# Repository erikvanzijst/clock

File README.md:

# 24H Digital Clock

This project contains the schematics and PCB layout for a 24-hour digital
quartz clock with self-dimming LED display.

Full write-up is at https://medium.com/@erikvanzijst/a-digital-quartz-clock-from-scratch-a80ec5e427

## Kicad symbol and footprint libraries
The project uses the [DigiKey Kicad symbol and footprint libraries](https://github.com/Digi-Key/digikey-kicad-library).
After cloning or downloading those locally, [add them to the Kicad Symbol and
Footprint libraries](https://forum.digikey.com/t/importing-the-digi-key-kicad-library-into-kicad-5-0-0/4075).

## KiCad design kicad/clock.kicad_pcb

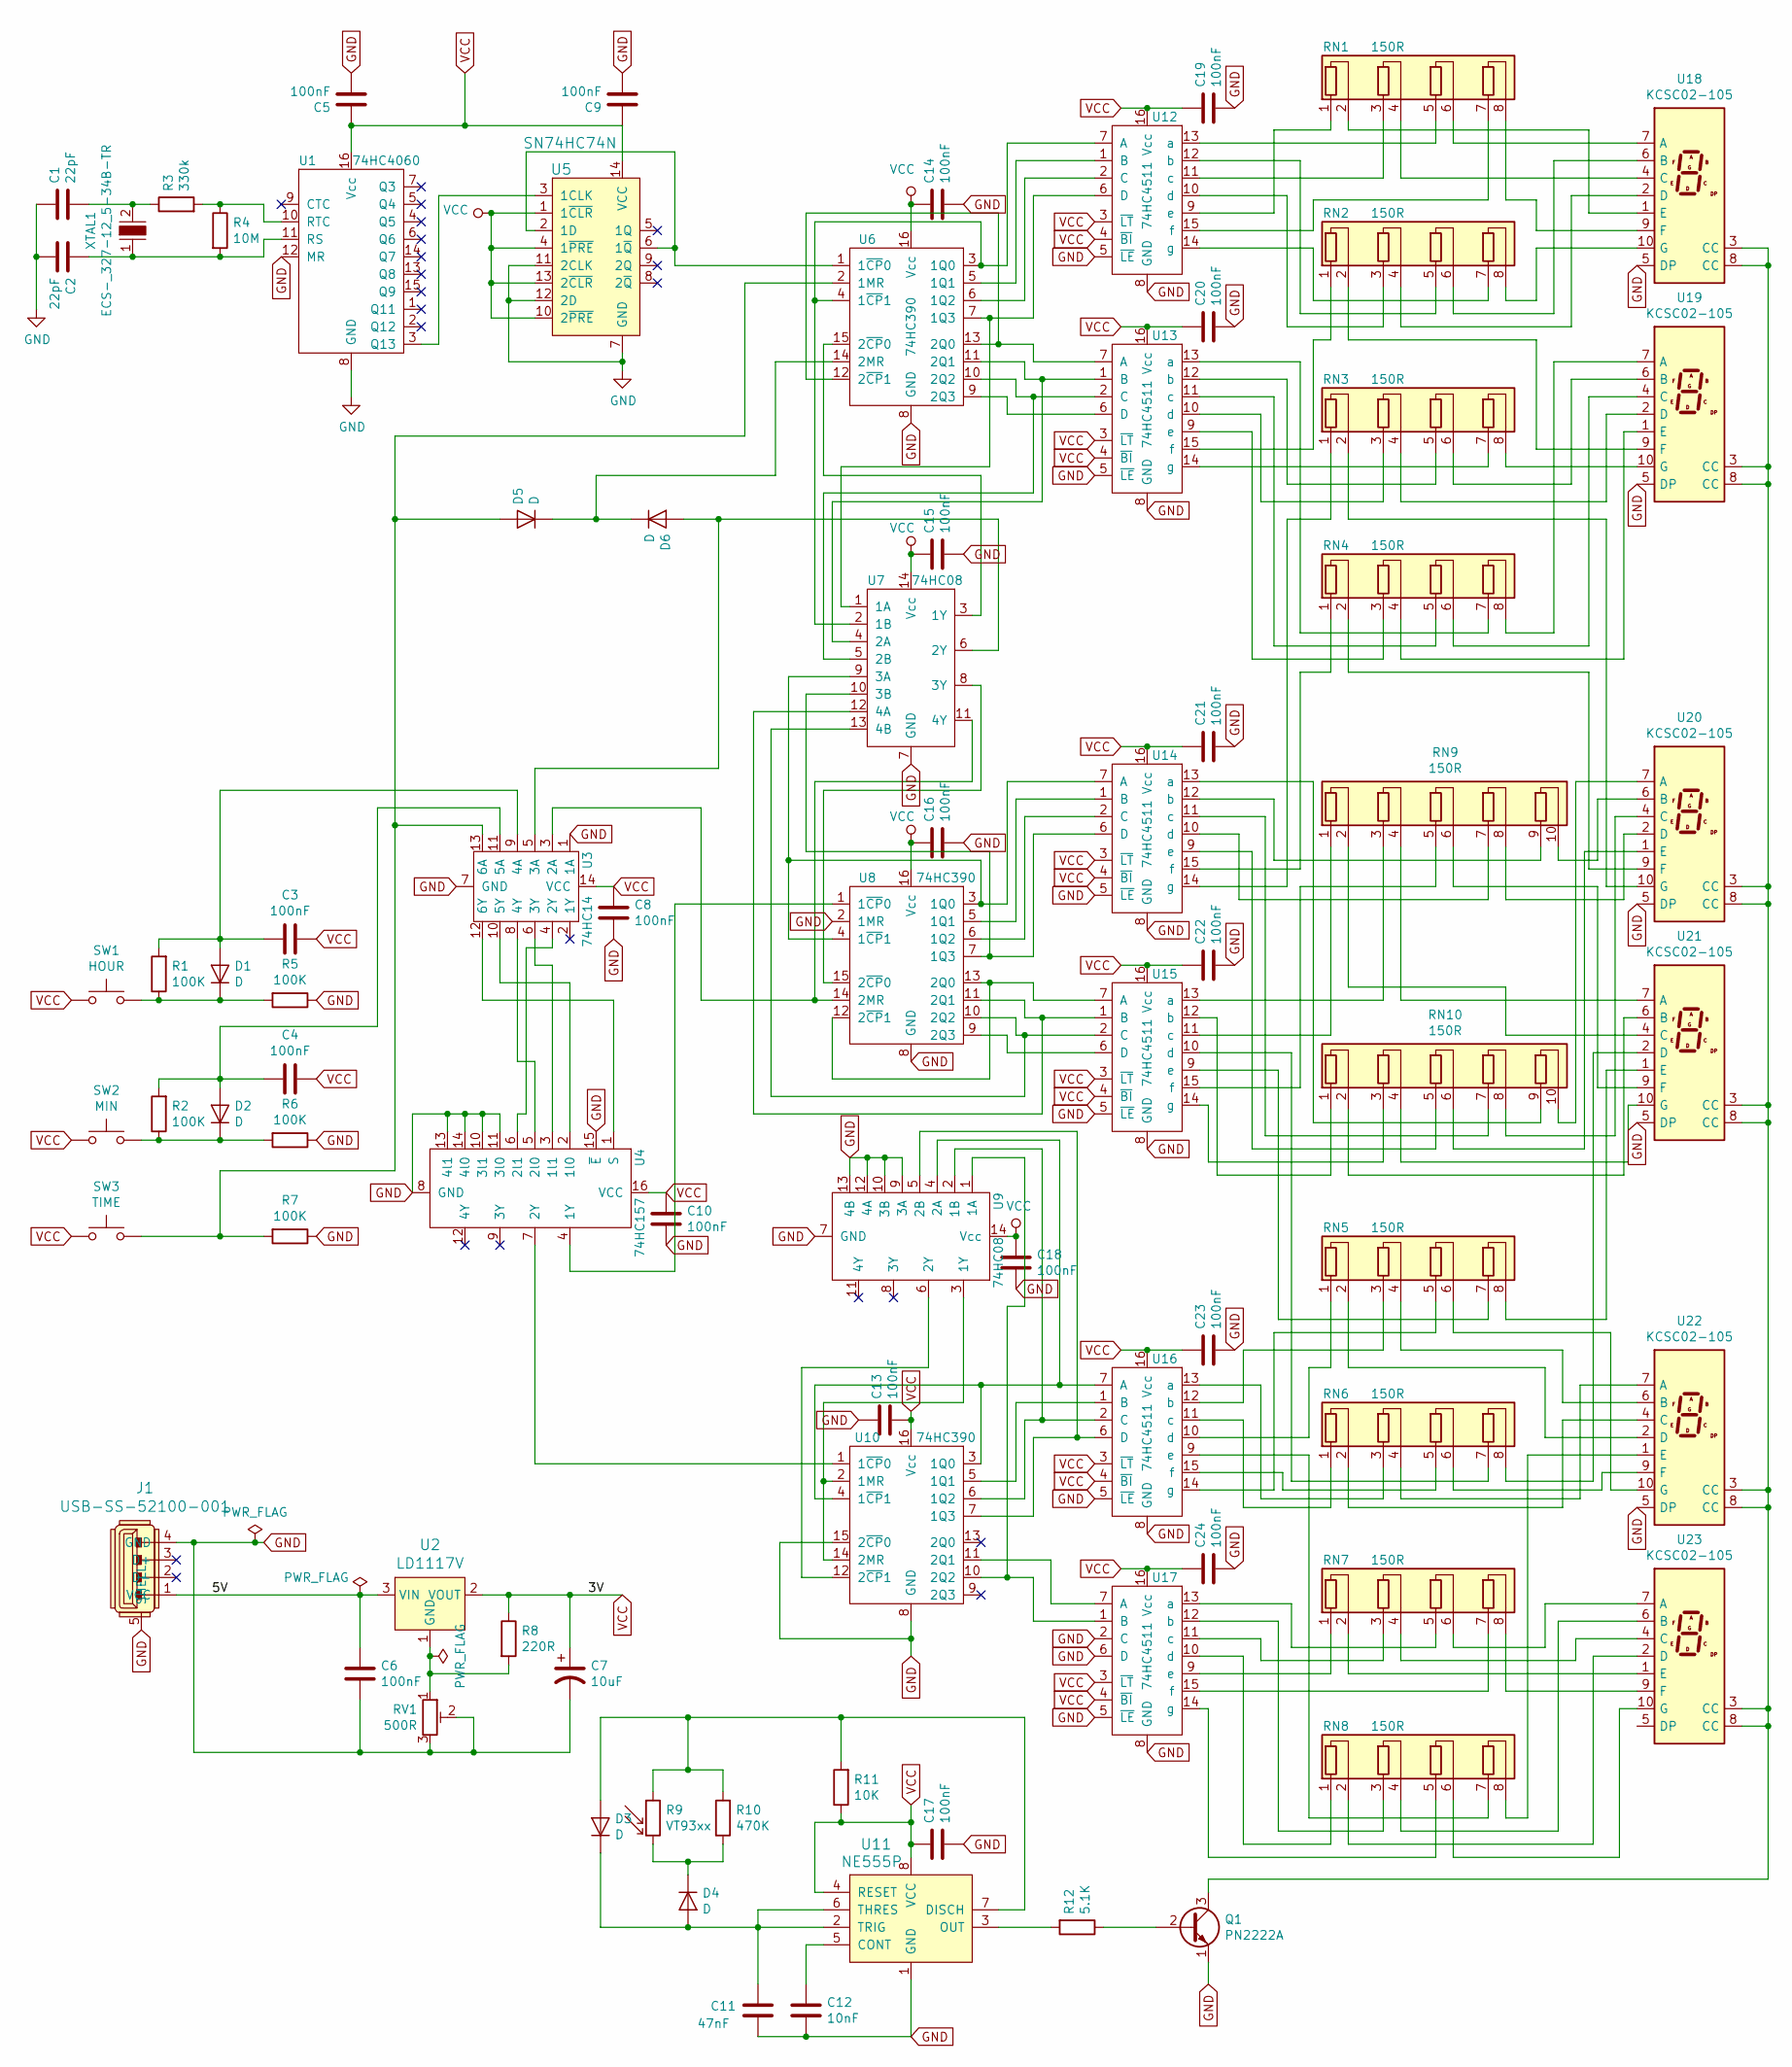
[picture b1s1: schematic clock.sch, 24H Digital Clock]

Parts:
C1, C2: 22pF; C_Disc_D5.0mm_W2.5mm_P2.50mm
C3, C4, C5, C6, C8, C9, C10, C13, C14, C15, C16, C17, C18, C19, C20, C21, C22, C23, C24: 100nF; C_Disc_D5.0mm_W2.5mm_P2.50mm
C7: 10uF; CP_Radial_Tantal_D5.0mm_P2.50mm
C11: 47nF; C_Disc_D5.0mm_W2.5mm_P2.50mm
C12: 10nF; C_Disc_D5.0mm_W2.5mm_P2.50mm
D1, D2, D3, D4, D5, D6: D; Diode_DO-35_P10mm
J1: USB-SS-52100-001; USB_A_Stewart_SS-52100-001_Horizontal; MPN SS-52100-001; Digi-Key_PN 380-1412-ND
Q1: PN2222A; TO-92_Inline_Wide
R1, R2, R5, R6, R7: 100K; R_Axial_DIN0207_L6.3mm_D2.5mm_P7.62mm_Horizontal
R3: 330k; R_Axial_DIN0207_L6.3mm_D2.5mm_P7.62mm_Horizontal
R4: 10M; R_Axial_DIN0207_L6.3mm_D2.5mm_P7.62mm_Horizontal
R8: 220R; R_Axial_DIN0207_L6.3mm_D2.5mm_P7.62mm_Horizontal
R9: VT93xx; R_LDR_4.9x4.2mm_P2.54mm_Vertical
R10: 470K; R_Axial_DIN0207_L6.3mm_D2.5mm_P7.62mm_Horizontal
R11: 10K; R_Axial_DIN0207_L6.3mm_D2.5mm_P7.62mm_Horizontal
R12: 5.1K; R_Axial_DIN0207_L6.3mm_D2.5mm_P7.62mm_Horizontal
RN1, RN2, RN3, RN4, RN5, RN6, RN7, RN8: 150R; R_Array_SIP8
RN9, RN10: 150R; R_Array_SIP10
RV1: 500R; Potentiometer_Bourns_3339P_Vertical_HandSoldering
SW1: HOUR; SW_PUSH_6mm_H4.3mm
SW2: MIN; SW_PUSH_6mm_H4.3mm
SW3: TIME; SW_PUSH_6mm_H4.3mm
U1: 74HC4060; DIP-16_W7.62mm_Socket
U2: LD1117V; TO-220-3; MPN LD1117V; Digi-Key_PN 497-7310-5-ND
U3: 74HC14; Socket_DIP-14_0.775in_Conn
U4: 74HC157; DIP-16_W7.62mm_Socket
U5: SN74HC74N; Socket_DIP-14_0.775in_Conn; MPN SN74HC74N; Digi-Key_PN 296-1602-5-ND
U6, U8, U10: 74HC390; DIP-16_W7.62mm_Socket
U7, U9: 74HC08; Socket_DIP-14_0.775in_Conn
U11: NE555P; DIP-8_W7.62mm_Socket; MPN NE555P; Digi-Key_PN 296-1411-5-ND
U12, U13, U14, U15, U16, U17: 74HC4511; DIP-16_W7.62mm_Socket
U18, U19, U20, U21, U22, U23: KCSC02-105; 7SegmentLED_LTS6760_LTS6780
XTAL1: ECS-_327-12_5-34B-TR; Crystal_DS26_D2.0mm_L6.0mm_Horizontal; MPN ECS-.327-12.5-34B-TR; Digi-Key_PN XC1617CT-ND

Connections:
/5V: C6.1, J1.1 (VCC), U2.3 (VIN)
GND: C1.1, C2.2, C5.2, C6.2, C7.2, C8.2, C9.2, C10.2, C11.2, C12.2, C13.1, C14.2, C15.2, C16.2, C17.2, C18.2, C19.2, C20.2, C21.2, C22.2, C23.2, C24.2, J1.4 (GND), J1.5 (SHELL), Q1.1 (E), R5.1, R6.1, R7.1, RV1.2, RV1.3, U1.8 (GND), U1.12 (MR), U3.1 (1A), U3.7 (GND), U4.8 (GND), U4.10 (3l1), U4.11 (3l0), U4.13 (4l1), U4.14 (4l0), U4.15 (~E), U5.7 (GND), U5.11 (2CLK), U5.12 (2D), U6.8 (GND), U7.7 (GND), U8.2 (1MR), U8.8 (GND), U9.7 (GND), U9.9 (3A), U9.10 (3B), U9.12 (4A), U9.13 (4B), U10.8 (GND), U10.15 (2~CP~0), U11.1 (GND), U12.5 (~LE), U12.8 (GND), U13.5 (~LE), U13.8 (GND), U14.5 (~LE), U14.8 (GND), U15.5 (~LE), U15.8 (GND), U16.5 (~LE), U16.8 (GND), U17.2 (C), U17.5 (~LE), U17.6 (D), U17.8 (GND), U18.5 (DP), U19.5 (DP), U20.5 (DP), U21.5 (DP), U22.5 (DP)
unnamed: C1.2, R3.1, XTAL1.2
unnamed: C2.1, R4.2, U1.11 (RS), XTAL1.1
unnamed: C3.2, D1.2 (A), R1.2, U3.9 (4A)
unnamed: C4.2, D2.2 (A), R2.2, U3.11 (5A)
unnamed: C11.1, D3.1 (K), D4.2 (A), U11.2 (TRIG), U11.6 (THRES)
unnamed: C12.1, U11.5 (CONT)
unnamed: D1.1 (K), R1.1, R5.2, SW1.2
unnamed: D2.1 (K), R2.1, R6.2, SW2.2
unnamed: D3.2 (A), R9.1, R10.2, R11.2, U11.7 (DISCH)
unnamed: D4.1 (K), R9.2, R10.1
unnamed: D5.1 (K), D6.1 (K), U6.14 (2MR)
unnamed: D5.2 (A), R7.2, SW3.2, U3.13 (6A), U6.2 (1MR)
unnamed: D6.2 (A), U3.5 (3A), U7.6 (2Y)
unnamed: Q1.2 (B), R12.1
unnamed: Q1.3 (C), U18.3 (CC), U18.8 (CC), U19.3 (CC), U19.8 (CC), U20.3 (CC), U20.8 (CC), U21.3 (CC), U21.8 (CC), U22.3 (CC), U22.8 (CC), U23.3 (CC), U23.8 (CC)
unnamed: R3.2, R4.1, U1.10 (RTC)
unnamed: R8.2, RV1.1, U2.1 (GND)
unnamed: R12.2, U11.3 (OUT)
unnamed: RN1.1 (R1.1), U12.9 (e)
unnamed: RN1.2 (R1.2), U18.1 (E)
unnamed: RN1.3 (R2.1), U12.11 (c)
unnamed: RN1.4 (R2.2), U18.4 (C)
unnamed: RN1.5 (R3.1), U12.13 (a)
unnamed: RN1.6 (R3.2), U18.7 (A)
unnamed: RN1.7 (R4.1), U12.15 (f)
unnamed: RN1.8 (R4.2), U18.9 (F)
unnamed: RN2.1 (R1.1), U13.15 (f)
unnamed: RN2.2 (R1.2), U19.9 (F)
unnamed: RN2.3 (R2.1), U12.10 (d)
unnamed: RN2.4 (R2.2), U18.2 (D)
unnamed: RN2.5 (R3.1), U12.12 (b)
unnamed: RN2.6 (R3.2), U18.6 (B)
unnamed: RN2.7 (R4.1), U12.14 (g)
unnamed: RN2.8 (R4.2), U18.10 (G)
unnamed: RN3.1 (R1.1), U14.14 (g)
unnamed: RN3.2 (R1.2), U20.10 (G)
unnamed: RN3.3 (R2.1), U13.10 (d)
unnamed: RN3.4 (R2.2), U19.2 (D)
unnamed: RN3.5 (R3.1), U13.12 (b)
unnamed: RN3.6 (R3.2), U19.6 (B)
unnamed: RN3.7 (R4.1), U13.14 (g)
unnamed: RN3.8 (R4.2), U19.10 (G)
unnamed: RN4.1 (R1.1), U14.15 (f)
unnamed: RN4.2 (R1.2), U20.9 (F)
unnamed: RN4.3 (R2.1), U13.9 (e)
unnamed: RN4.4 (R2.2), U19.1 (E)
unnamed: RN4.5 (R3.1), U13.11 (c)
unnamed: RN4.6 (R3.2), U19.4 (C)
unnamed: RN4.7 (R4.1), U13.13 (a)
unnamed: RN4.8 (R4.2), U19.7 (A)
unnamed: RN5.1 (R1.1), U16.10 (d)
unnamed: RN5.2 (R1.2), U22.2 (D)
unnamed: RN5.3 (R2.1), U16.12 (b)
unnamed: RN5.4 (R2.2), U22.6 (B)
unnamed: RN5.5 (R3.1), U16.14 (g)
unnamed: RN5.6 (R3.2), U22.10 (G)
unnamed: RN5.7 (R4.1), U15.9 (e)
unnamed: RN5.8 (R4.2), U21.1 (E)
unnamed: RN6.1 (R1.1), U16.11 (c)
unnamed: RN6.2 (R1.2), U22.4 (C)
unnamed: RN6.3 (R2.1), U16.13 (a)
unnamed: RN6.4 (R2.2), U22.7 (A)
unnamed: RN6.5 (R3.1), U16.15 (f)
unnamed: RN6.6 (R3.2), U22.9 (F)
unnamed: RN6.7 (R4.1), U15.10 (d)
unnamed: RN6.8 (R4.2), U21.2 (D)
unnamed: RN7.1 (R1.1), U17.9 (e)
unnamed: RN7.2 (R1.2), U23.1 (E)
unnamed: RN7.3 (R2.1), U17.11 (c)
unnamed: RN7.4 (R2.2), U23.4 (C)
unnamed: RN7.5 (R3.1), U17.13 (a)
unnamed: RN7.6 (R3.2), U23.7 (A)
unnamed: RN7.7 (R4.1), U17.15 (f)
unnamed: RN7.8 (R4.2), U23.9 (F)
unnamed: RN8.1 (R1.1), U17.10 (d)
unnamed: RN8.2 (R1.2), U23.2 (D)
unnamed: RN8.3 (R2.1), U17.12 (b)
unnamed: RN8.4 (R2.2), U23.6 (B)
unnamed: RN8.5 (R3.1), U17.14 (g)
unnamed: RN8.6 (R3.2), U23.10 (G)
unnamed: RN8.7 (R4.1), U16.9 (e)
unnamed: RN8.8 (R4.2), U22.1 (E)
unnamed: RN9.1 (R1.1), U15.11 (c)
unnamed: RN9.2 (R1.2), U21.4 (C)
unnamed: RN9.3 (R2.1), U15.13 (a)
unnamed: RN9.4 (R2.2), U21.7 (A)
unnamed: RN9.5 (R3.1), U15.15 (f)
unnamed: RN9.6 (R3.2), U21.9 (F)
unnamed: RN9.7 (R4.1), U14.10 (d)
unnamed: RN9.8 (R4.2), U20.2 (D)
unnamed: RN9.9 (R5.1), U14.12 (b)
unnamed: RN9.10 (R5.2), U20.6 (B)
unnamed: RN10.1 (R1.1), U15.12 (b)
unnamed: RN10.2 (R1.2), U21.6 (B)
unnamed: RN10.3 (R2.1), U15.14 (g)
unnamed: RN10.4 (R2.2), U21.10 (G)
unnamed: RN10.5 (R3.1), U14.9 (e)
unnamed: RN10.6 (R3.2), U20.1 (E)
unnamed: RN10.7 (R4.1), U14.11 (c)
unnamed: RN10.8 (R4.2), U20.4 (C)
unnamed: RN10.9 (R5.1), U14.13 (a)
unnamed: RN10.10 (R5.2), U20.7 (A)
unnamed: U1.3 (Q13), U5.3 (1CLK)
unnamed: U3.3 (2A), U7.11 (4Y), U8.14 (2MR)
unnamed: U3.4 (2Y), U4.6 (2l1)
unnamed: U3.6 (3Y), U4.3 (1l1)
unnamed: U3.8 (4Y), U4.5 (2l0)
unnamed: U3.10 (5Y), U4.2 (1l0)
unnamed: U3.12 (6Y), U4.1 (S)
unnamed: U4.4 (1Y), U8.1 (1~CP~0)
unnamed: U5.2 (1D), U5.6 (1~Q), U6.1 (1~CP~0)
unnamed: U6.15 (2~CP~0), U7.3 (1Y)
unnamed: U7.8 (3Y), U8.15 (2~CP~0)
unnamed: U4.7 (2Y), U10.1 (1~CP~0)
unnamed: U9.4 (2A), U10.3 (1Q0), U10.4 (1~CP~1), U16.7 (A)
unnamed: U10.5 (1Q1), U16.1 (B)
unnamed: U9.2 (1B), U10.6 (1Q2), U16.2 (C)
unnamed: U9.5 (2B), U10.7 (1Q3), U16.6 (D)
unnamed: U9.1 (1A), U10.10 (2Q2), U17.1 (B)
unnamed: U10.11 (2Q1), U17.7 (A)
unnamed: U9.6 (2Y), U10.12 (2~CP~1)
unnamed: U9.3 (1Y), U10.2 (1MR), U10.14 (2MR)
unnamed: U6.5 (1Q1), U12.1 (B)
unnamed: U6.6 (1Q2), U12.2 (C)
unnamed: U6.7 (1Q3), U7.1 (1A), U12.6 (D)
unnamed: U6.3 (1Q0), U6.4 (1~CP~1), U7.2 (1B), U12.7 (A)
unnamed: U6.11 (2Q1), U7.4 (2A), U13.1 (B)
unnamed: U6.10 (2Q2), U7.5 (2B), U13.2 (C)
unnamed: U6.9 (2Q3), U13.6 (D)
unnamed: U6.12 (2~CP~1), U6.13 (2Q0), U13.7 (A)
unnamed: U8.5 (1Q1), U14.1 (B)
unnamed: U8.6 (1Q2), U14.2 (C)
unnamed: U7.10 (3B), U8.7 (1Q3), U14.6 (D)
unnamed: U7.9 (3A), U8.3 (1Q0), U8.4 (1~CP~1), U14.7 (A)
unnamed: U7.12 (4A), U8.11 (2Q1), U15.1 (B)
unnamed: U7.13 (4B), U8.10 (2Q2), U15.2 (C)
unnamed: U8.9 (2Q3), U15.6 (D)
unnamed: U8.12 (2~CP~1), U8.13 (2Q0), U15.7 (A)
VCC: C3.1, C4.1, C5.1, C7.1, C8.1, C9.1, C10.1, C13.2, C14.1, C15.1, C16.1, C17.1, C18.1, C19.1, C20.1, C21.1, C22.1, C23.1, C24.1, R8.1, R11.1, SW1.1, SW2.1, SW3.1, U1.16 (Vcc), U2.2 (VOUT), U3.14 (VCC), U4.16 (VCC), U5.1 (1~CLR), U5.4 (1~PRE), U5.10 (2~PRE), U5.13 (2~CLR), U5.14 (VCC), U6.16 (Vcc), U7.14 (Vcc), U8.16 (Vcc), U9.14 (Vcc), U10.16 (Vcc), U11.4 (RESET), U11.8 (VCC), U12.3 (~LT), U12.4 (~BI), U12.16 (Vcc), U13.3 (~LT), U13.4 (~BI), U13.16 (Vcc), U14.3 (~LT), U14.4 (~BI), U14.16 (Vcc), U15.3 (~LT), U15.4 (~BI), U15.16 (Vcc), U16.3 (~LT), U16.4 (~BI), U16.16 (Vcc), U17.3 (~LT), U17.4 (~BI), U17.16 (Vcc)

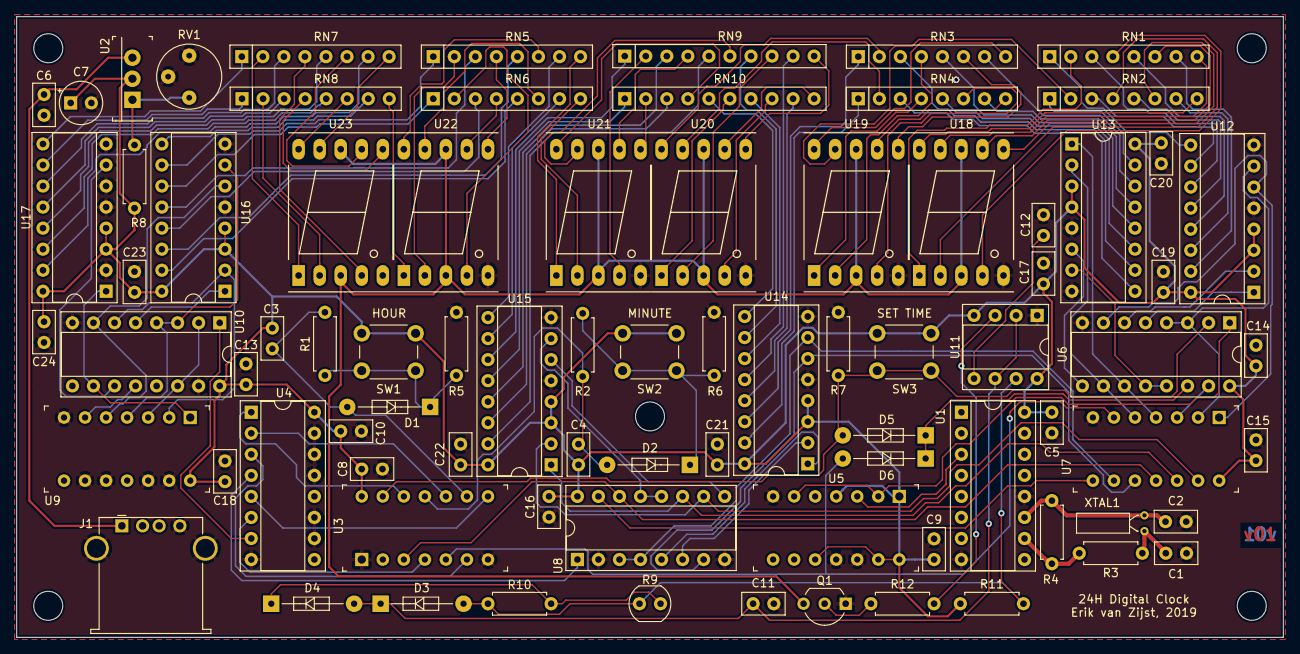
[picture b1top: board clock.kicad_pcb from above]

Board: 2 copper layers, 152.9 x 74.9 mm, 82 parts (0 on the bottom side), 141 nets.

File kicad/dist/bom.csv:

Reference, Quantity, Value,MPN,Digikey Part Number,Price,Total Price,Part Page, Footprint, Category, DK_Datasheet_Link, DK_Detail_Page, Description, Digi-Key_PN, Family, MPN, Manufacturer, Status
C11 ,1,47nF,,,,,,Capacitor_THT:C_Disc_D5.0mm_W2.5mm_P2.50mm,,,,,,,,,
C12 ,1,10nF,,,,,,Capacitor_THT:C_Disc_D5.0mm_W2.5mm_P2.50mm,,,,,,,,,
C2 C1 ,2,22pF,,,,,,Capacitor_THT:C_Disc_D5.0mm_W2.5mm_P2.50mm,,,,,,,,,
C4 C3 C5 C14 C15 C21 C16 C22 C8 C10 C18 C23 C13 C17 C9 C19 C20 C24 ,18,100nF,C320C104J5R5TA,399-9775-ND,$0.48,,https://www.digikey.com/product-detail/en/kemet/C320C104J5R5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,Capacitor_THT:C_Disc_D5.0mm_W2.5mm_P2.50mm,,,,,,,,,
C6 ,1,10uF,,,,,,Capacitor_THT:C_Disc_D5.0mm_W2.5mm_P2.50mm,,,,,,,,,
C7 ,1,10uF,,,,,,Capacitor_THT:C_Radial_D5.0mm_H11.0mm_P2.00mm,,,,,,,,,
D1 D2 D3 D4 ,4,D,,,,,,digikey-footprints:Diode_DO-35_P10mm,,,,,,,,,
J1 ,1,USB-SS-52100-001,SS-52100-001,380-1412-ND,$0.44,,https://www.digikey.com/products/en?keywords=380-1412-ND,KiCad:USB_A_Stewart_SS-52100-001_Horizontal,"Connectors, Interconnects",,https://www.digikey.com/product-detail/en/stewart-connector/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,CONN RCPT USB2.0 TYPEA 4POS R/A,380-1412-ND,"USB, DVI, HDMI Connectors",SS-52100-001,Stewart Connector,Active
Q1 ,1,PN2222A,,,,,,Package_TO_SOT_THT:TO-92_Inline_Wide,,,,,,,,,
R10 ,1,10K,,,,,,Resistor_THT:R_Axial_DIN0207_L6.3mm_D2.5mm_P7.62mm_Horizontal,,,,,,,,,
R11 ,1,5.1K,,,,,,Resistor_THT:R_Axial_DIN0207_L6.3mm_D2.5mm_P7.62mm_Horizontal,,,,,,,,,
R3 ,1,330k,SFR2500003303JA500,BC4849CT-ND,$0.13,,https://www.digikey.com/product-detail/en/vishay-bc-componen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,Resistor_THT:R_Axial_DIN0207_L6.3mm_D2.5mm_P7.62mm_Horizontal,,,,,,,,,
R4 ,1,10M,CF14JT10M0,CF14JT10M0CT-ND,$0.10,,https://www.digikey.com/product-detail/en/stackpole-electron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,Resistor_THT:R_Axial_DIN0207_L6.3mm_D2.5mm_P7.62mm_Horizontal,,,,,,,,,
R6 R2 R5 R1 ,4,100K,SFR2500001003FR500,PPC100KYCT-ND,$0.13,,https://www.digikey.com/products/en/resistors/through-hole-r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,Resistor_THT:R_Axial_DIN0207_L6.3mm_D2.5mm_P7.62mm_Horizontal,,,,,,,,,
R7 ,1,220R,SFR2500002200FR500,PPC220YCT-ND,$0.13,,https://www.digikey.com/product-detail/en/vishay-bc-componen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,Resistor_THT:R_Axial_DIN0207_L6.3mm_D2.5mm_P7.62mm_Horizontal,,,,,,,,,
R8 ,1,VT93xx,PDV-P7002,PDV-P7002-ND,$1.41,,https://www.digikey.com/product-detail/en/advanced-photonix/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,OptoDevice:R_LDR_4.9x4.2mm_P2.54mm_Vertical,,,,,,,,,
R9 ,1,1M,,,,,,Resistor_THT:R_Axial_DIN0207_L6.3mm_D2.5mm_P7.62mm_Horizontal,,,,,,,,,
RN1 RN2 RN3 RN4 RN5 RN6 RN7 RN8 ,8,150R,4608X-102-151LF,4608X-2-151LF-ND,$0.57,,https://www.digikey.com/product-detail/en/4608X-102-151LF/46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,Resistor_THT:R_Array_SIP8,,,,,,,,,
RN9 RN10 ,2,150R,4610X-102-151LF,4610X-2-151LF-ND,$0.58,,https://www.digikey.com/product-detail/en/4610X-102-151LF/46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,Resistor_THT:R_Array_SIP10,,,,,,,,,
RV1 ,1,500R,3362P-1-501LF,3362P-501LF-ND,$1.02,,https://www.digikey.com/product-detail/en/3362P-1-501LF/3362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,Potentiometer_THT:Potentiometer_Bourns_3339P_Vertical_HandSoldering,,,,,,,,,
SW1 ,1,HOUR,,,,,,Button_Switch_THT:SW_PUSH_6mm_H4.3mm,,,,,,,,,
SW2 ,1,MIN,,,,,,Button_Switch_THT:SW_PUSH_6mm_H4.3mm,,,,,,,,,
SW3 ,1,TIME,,,,,,Button_Switch_THT:SW_PUSH_6mm_H4.3mm,,,,,,,,,
U1 ,1,74HC4060,SN74HC4060N,296-8209-5-ND,$0.58,,https://www.digikey.com/product-detail/en/texas-instruments/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,Package_DIP:DIP-16_W7.62mm_Socket,,,,,,,,,
U11 ,1,NE555P,NE555P,296-1411-5-ND,$0.45,,https://www.digikey.com/product-detail/en/NE555P/296-1411-5-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,Package_DIP:DIP-8_W7.62mm_Socket,Integrated Circuits (ICs),http://www.ti.com/general/docs/suppproductinfo.tsp?distId=10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,/product-detail/en/texas-instruments/NE555P/296-1411-5-ND/277057,IC OSC SINGLE TIMER 100KHZ 8-DIP,296-1411-5-ND,Clock/Timing - Programmable Timers and Oscillators,NE555P,Texas Instruments,Active
U12 U14 U15 U16 U13 U17 ,6,74HC4511,CD74HC4511E,296-14537-5-ND,$0.85,,https://www.digikey.com/product-detail/en/texas-instruments/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,Package_DIP:DIP-16_W7.62mm_Socket,,,,,,,,,
U18 U19 U20 U21 U23 U22 ,6,KCSC02-105,,,,,https://www.velleman.eu/downloads/29/infosheets/vmp502_sma42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,Display_7Segment:7SegmentLED_LTS6760_LTS6780,,,,,,,,,
U2 ,1,LD1117V,LD1117V,497-7310-5-ND,$0.55,,https://www.digikey.com/product-detail/en/LD1117V/497-7310-5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,digikey-footprints:TO-220-3,Integrated Circuits (ICs),http://www.st.com/content/ccc/resource/technical/document/da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,/product-detail/en/stmicroelectronics/LD1117V33/497-1491-5-ND/586012,IC REG LINEAR 1.8V-5V 800MA TO220AB,497-7310-5-ND,PMIC - Voltage Regulators - Linear,LD1117V,STMicroelectronics,Active
U3 ,1,74HC14,SN74HC14N,296-1577-5-ND,$0.55,,https://www.digikey.com/product-detail/en/texas-instruments/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,clock:Socket_DIP-14_0.775in_Conn,,,,,,,,,
U4 ,1,74HC157,SN74HC157N,296-1578-5-ND,$0.50,,https://www.digikey.com/product-detail/en/SN74HC157N/296-157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,Package_DIP:DIP-16_W7.62mm_Socket,,,,,,,,,
U5 ,1,SN74HC74N,SN74HC74N,296-1602-5-ND,$0.48,,https://www.digikey.com/product-detail/en/texas-instruments/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,clock:Socket_DIP-14_0.775in_Conn,Integrated Circuits (ICs),http://www.ti.com/general/docs/suppproductinfo.tsp?distId=10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,/product-detail/en/texas-instruments/SN74HC74N/296-1602-5-ND/277248,IC FF D-TYPE DUAL 1BIT 14DIP,296-1602-5-ND,Logic - Flip Flops,SN74HC74N,Texas Instruments,Active
U6 U8 U10 ,3,74HC390,CD74HC390E,296-9199-5-ND,$0.70,,https://www.digikey.com/product-detail/en/texas-instruments/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,Package_DIP:DIP-16_W7.62mm_Socket,,,,,,,,,
U9 U7 ,2,74HC08,,,,,,clock:Socket_DIP-14_0.775in_Conn,,,,,,,,,
XTAL1 ,1,ECS-_327-12_5-34B-TR,ECS-.327-CDX-1038,XC2121-ND,$0.60,,https://www.digikey.com/product-detail/en/ecs-inc/ECS-.327-C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,Crystal:Crystal_DS26_D2.0mm_L6.0mm_Horizontal,"Crystals, Oscillators, Resonators",http://www.ecsxtal.com/store/pdf/ecx-31b.pdf,/product-detail/en/ecs-inc/ECS-.327-12.5-34B-TR/XC1617CT-ND/1693786,CRYSTAL 32.7680KHZ 12.5PF SMD,XC1617CT-ND,Crystals,ECS-.327-12.5-34B-TR,ECS Inc.,Active
DIP Socket 8 Pins,1,DIP Socket 8 Pins,ED08DT,ED3044-5-ND,$0.16,,https://www.digikey.com/product-detail/en/on-shore-technolog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,,,,,,,,,,
DIP Socket 14 Pins,4,DIP Socket 14 Pins,A 14-LC-TT,AE9989-ND,$0.22,,https://www.digikey.com/product-detail/en/assmann-wsw-compon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,,,,,,,,,,
DIP Socket 16 Pins,11,DIP Socket 16 Pins,ED16DT,ED3046-5-ND,$0.19,,https://www.digikey.com/product-detail/en/on-shore-technolog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,,,,,,,,,,

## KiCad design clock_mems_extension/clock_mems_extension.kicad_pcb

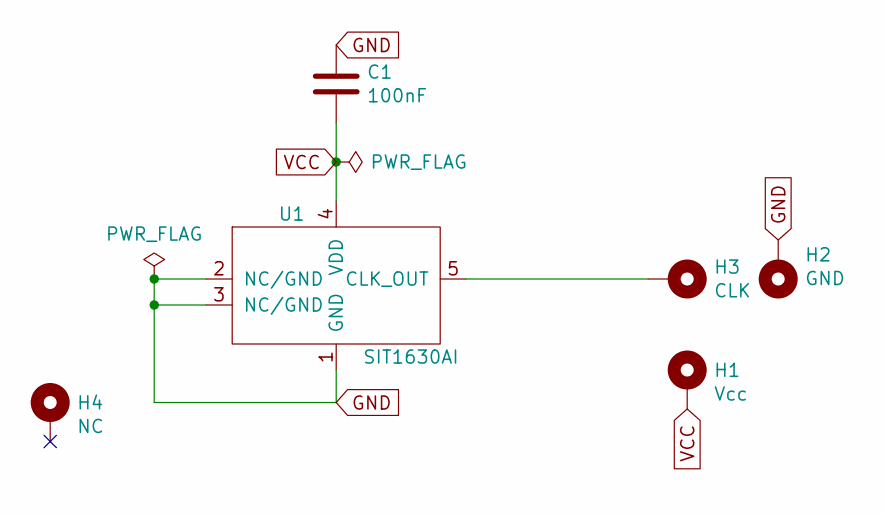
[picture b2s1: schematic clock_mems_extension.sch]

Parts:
C1: 100nF; C_0603_1608Metric_Pad1.05x0.95mm_HandSolder
H1: Vcc; Pin_D0.8mm
H2: GND; Pin_D0.8mm
H3: CLK; Pin_D0.8mm
H4: NC; Pin_D0.8mm
U1: SIT1630AI; SOT-23-5_HandSoldering

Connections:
GND: C1.1, H2.1, U1.1 (GND), U1.2 (NC/GND), U1.3 (NC/GND)
unnamed: H3.1, U1.5 (CLK_OUT)
VCC: C1.2, H1.1, U1.4 (VDD)

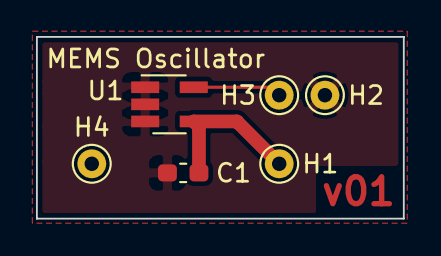
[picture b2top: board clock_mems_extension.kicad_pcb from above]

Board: 2 copper layers, 20.4 x 10.1 mm, 6 parts (0 on the bottom side), 3 nets.

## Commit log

2019-12-29 Initial commit of the restructured project
    Pulled the project out of the github.com/erikvanzijst/electronics repo to give it
    a location of its own in accordance with the URL printed on the PCB.
2020-01-12 README: Added link to blog post
    Added a link to the Medium post with the full project write-up.

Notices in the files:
kicad/clock.kicad_pcb:
License: BY CC 4.0
kicad/clock.sch:
creativecommons.org/licenses/by/4.0
License: CC BY 4.0
